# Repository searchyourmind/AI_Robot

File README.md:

# AI Robot — Raspberry Pi Vision & Motor Control

AI Robot is a four-wheel Raspberry Pi robot project combining motor control, live camera video, a browser driving interface, and AI-assisted visual observation. A shared HTTP motor service connects the browser, command-line controller, and vision process, so camera processing and user interfaces can evolve independently of motor control.

The robot platform uses a **Raspberry Pi 5, four geared DC motors, two TB6612FNG dual-channel driver boards, a Pi Camera, a USB microphone, and a speaker**. This repository contains the Python services, control logic, tests, wiring documentation, and a custom four-motor interface PCB design.

## What the project includes

- **Motor control service:** a Flask API for direction, speed, short movement commands, stopping, and control ownership.
- **Live camera and browser interface:** MJPEG video, a latest-frame snapshot endpoint, directional buttons, a speed slider, and explicit reset/arm controls.
- **Vision policy:** camera snapshots are sent to a vision model for person and stop-sign observations. An annotated video stream shows the result; the current policy can request a stop and does not initiate movement.
- **Command-line control:** a text interface for the same motor API, including speed changes and short directional commands. The `voice_ai_motor_simple.py` filename comes from earlier voice-control work; this script is currently a manual CLI.
- **Motor interface PCB:** editable KiCad schematics and layout, component selection, power calculations, wiring diagrams, BOM, and fabrication-format exports for a 12 V-class redesign.
- **Offline verification:** injected-clock and fake-GPIO tests cover the control state machine, API, clients, camera interfaces, vision parsing, and the Rev A backend lifecycle.

The motor service defaults to an in-memory **mock backend**. An opt-in **Raspberry Pi 5 / Rev A DRV8874 backend** drives the new board's GPIO, PWM, RUN, ARM, and watchdog heartbeat interface. It controls four separate bridges in left/right pairs. The backend has offline verification; the Rev A board remains a design-stage subsystem and the electrical behavior has not been bench-validated. This backend does not use the existing TB6612 harness. See the [Rev A backend guide](pi_robot/DRV8874_REVA.md).

A second opt-in backend, **`tb6612_dual`**, drives the prototype as built: two TB6612FNG boards wired directly to the Pi 5. It requires an explicit pin and polarity configuration and a duty ceiling, and ramps speed increases. It is verified offline and **has not been run on the robot**; see the [setup and first bench session](pi_robot/TB6612_DUAL.md).

## System architecture

```mermaid
flowchart LR
    CAMERA[Pi Camera] --> VIDEO[Camera service · 8090]
    VIDEO -->|MJPEG video| BROWSER[Browser controls]
    VIDEO -->|Timestamped JPEG snapshot| VISION[Vision policy · 8091]
    MODEL[Vision model] <--> VISION
    VISION --> OVERLAY[Annotated video]
    BROWSER -->|Same-origin command proxy| MOTOR[Motor API · 8088]
    CLI[Manual CLI] --> MOTOR
    VISION -->|Stop requests| MOTOR
    MOTOR --> CONTROL[Ownership / arm state / command deadlines]
    CONTROL --> BACKEND[Mock or Rev A DRV8874 backend]
    BACKEND -->|Opt-in GPIO / PWM / RUN / ARM / heartbeat| PCB[Four bridges · paired left/right commands]
```

The motor API is the command boundary. The browser and CLI request manual control; the vision process supplies observations and stop requests. A command belongs to one source/session and expires unless it is replaced by another valid command. Stopping or expiry clears the control lease. This keeps UI state, camera processing, and motor state explicit across separate processes.

## Robot hardware

| Subsystem | Project hardware |
| --- | --- |
| Compute | Raspberry Pi 5, 4 GB camera kit |
| Drivetrain | Two WHEELTEC R3 two-wheel chassis sets, giving four geared DC motors |
| Motor purchase specification | 12 V, 30:1 reduction, 500-line GMR encoder version |
| Motor drivers | Two TB6612FNG dual-channel boards |
| Batteries purchased | Two packs listed as 12 V, 2500 mAh, with built-in protection |
| Vision | Pi Camera, accessed by the camera service through OpenCV |
| Audio | USB microphone and speaker for voice-interaction experiments |

Each driver channel has its own motor connection:

| Existing driver | Channel A | Channel B |
| --- | --- | --- |
| Board A | Front-left motor | Front-right motor |
| Board B | Back-left motor | Back-right motor |

The Pi controls the existing driver boards directly; there is no Arduino in the motor-control loop. The Pi has separate power, while the motor source feeds the drivers' VM inputs. Pi ground, driver grounds, and motor-battery negative share a reference. The installed arrangement of the two purchased packs and the complete GPIO harness still need to be recorded. The purchased encoders are not yet integrated into wheel-speed feedback.

The exact motor label is still unconfirmed; MG513P30_12V is a candidate, not an established part number. Pack chemistry and actual minimum/maximum voltage also remain open. The [hardware record](hardware/rev_a/docs/actual_hardware_evidence.md) and [wiring guide](hardware/rev_a/docs/wiring_guide.md) separate the known connections from these remaining details.

## Software modules

| File | Role |
| --- | --- |
| [`web_motor.py`](pi_robot/web_motor.py) | Flask `/cmd` and `/status` endpoints; motor-service lifecycle |
| [`motor_control.py`](pi_robot/motor_control.py) | Ownership, arming, command validation, deadlines, and stop state |
| [`motor_backend.py`](pi_robot/motor_backend.py) | Backend lifecycle interface and mock motor outputs |
| [`drv8874_backend.py`](pi_robot/drv8874_backend.py) | Pi 5 GPIO, paired PWM/DIR, explicit ARM, and health-gated heartbeat for Rev A |
| [`tb6612_backend.py`](pi_robot/tb6612_backend.py) | Pi 5 GPIO for the prototype's two TB6612FNG boards: STBY, PWM/IN1/IN2, duty ceiling, and ramped starts |
| [`motor_runtime.py`](pi_robot/motor_runtime.py) | Explicit backend selection and validated hardware configuration |
| [`motor_config.py`](pi_robot/motor_config.py) | Command bounds, timeouts, and motor configuration |
| [`web_vision_drive_picam_ai.py`](pi_robot/web_vision_drive_picam_ai.py) | Camera worker, video/snapshot routes, browser UI, and motor proxy |
| [`vision_policy_daemon.py`](pi_robot/vision_policy_daemon.py) | Snapshot acquisition, model requests, observation age checks, and overlay stream |
| [`vision_safety.py`](pi_robot/vision_safety.py) | Strict observation parsing and stop-only policy |
| [`voice_ai_motor_simple.py`](pi_robot/voice_ai_motor_simple.py) | Interactive text controller using the motor API |

The camera service publishes `/stream.mjpg` for display and `/snapshot.jpg` for policy input. The policy checks frame identity and age before and after model inference. A stop sign, a near/mid-distance person, or invalid/stale input produces a stop request. A negative detection does not arm the robot or resume an earlier command. The policy's annotated output is available at `/overlay.mjpg`.

## Run the software

From the repository root, create a Python 3.10+ environment and install the application dependencies:

```sh
python3 -m venv .venv
source .venv/bin/activate
python -m pip install -r pi_robot/requirements.txt
```

Start the motor service in mock mode:

```sh
MOTOR_BACKEND=mock python pi_robot/web_motor.py
```

In another terminal using the same environment, start the CLI:

```sh
MOTOR_URL=http://127.0.0.1:8088 python pi_robot/voice_ai_motor_simple.py
```

A command sequence is:

```text
reset
arm
f
```

Send `f` within one second of `arm`; otherwise the idle lease expires. `f` requests 0.25 seconds of forward movement in the mock backend. Expiry latches stop; use `reset` and `arm` again for another movement. `s` stops and disarms; `q` stops and exits.

On a system with a configured camera, start the camera/browser service in a third terminal:

```sh
MOTOR_URL=http://127.0.0.1:8088 CAM_W=320 CAM_H=240 CAM_FPS=15 python pi_robot/web_vision_drive_picam_ai.py
```

Open `http://127.0.0.1:8090/` on that host for video and controls. The services bind to loopback by default. The [software guide](pi_robot/README.md) covers camera configuration, optional model startup, local access, environment variables, and the API. Camera startup opens a real device; motor behavior follows the separately selected backend. The [Rev A backend guide](pi_robot/DRV8874_REVA.md) covers explicit hardware configuration and first bench checks. Voice recognition, wake-word handling, and speech synthesis are not integrated into the current CLI.

## Tests

```sh
python -m pip install -r tests/hardware_mock/requirements.txt
python -m pytest tests/hardware_mock tests/hardware_gpio -q
```

The offline suites use injected clocks, fake GPIO, camera frames, HTTP/model responses, and motor outputs. Coverage includes invalid commands, ownership conflicts, expired leases, reversal sequencing, stop behavior, GPIO failures and cleanup, heartbeat/ARM sequencing, malformed vision results, stale frames, and client shutdown. These tests do not operate motors or qualify PWM timing. See the [test guide](tests/hardware_mock/README.md) and [vision integration details](docs/vision_safety_integration.md).

The combined suite passes **304 tests** (225 before the TB6612 backend was added); the [Rev A backend verification report](hardware/rev_a/validation/drv8874_backend_test_report.md) records the checks and physical validation still required.

## Custom motor-control PCB

The PCB work consolidates the prototype's jumper-wire motor, power, and control connections. A hardware-record review corrected an initial 6 V assumption to a 12 V-class design. The current board uses **four DRV8874 bridges**, one per motor, with individual current regulation, a protected common motor input, and hardware watchdog/arming logic. Front and rear motors remain commanded together by side; their power outputs are separate.

The editable design has seven schematic sheets, a provisional 100 × 100 mm two-layer layout, 121 fitted components, and 14 copper testpoints. Native checks report **ERC 0, DRC 0, unconnected 0, and schematic parity 0**. The board is a design-stage subsystem; matching it to the installed motors, packs, harness, and chassis is part of the remaining integration work.

[KiCad project and board documentation](hardware/rev_a/README.md) · [Schematic PDF](hardware/rev_a/exports/draft/schematic.pdf) · [PCB PDF](hardware/rev_a/exports/draft/pcb_layout.pdf) · [BOM](hardware/rev_a/exports/draft/bom_fitted.csv) · [3D view](hardware/rev_a/exports/draft/views/kicad_3d_render.png)

## Project documentation and next steps

- [Software setup and API](pi_robot/README.md)
- [Rev A DRV8874 hardware backend](pi_robot/DRV8874_REVA.md)
- [TB6612 prototype hardware backend and first bench session](pi_robot/TB6612_DUAL.md)
- [Project development and design decisions](docs/project_development.md)
- [Camera, vision, and client integration](docs/vision_safety_integration.md)
- [Existing and proposed wiring](hardware/rev_a/docs/wiring_guide.md)
- [Motor-driver selection](hardware/rev_a/docs/driver_margin_review.md) and [power-path design](hardware/rev_a/docs/power_path_review_12v.md)
- [PCB checks and source identities](hardware/rev_a/validation/design/design_check_report.md)

The next integration steps are to finish the actual motor/battery/harness record, bench-validate the Rev A GPIO backend and board together, integrate encoder feedback, and evaluate the custom PCB against the robot's electrical and mechanical requirements. Camera timing, vision response, motor behavior, and the audio interface remain separate areas for continued development.

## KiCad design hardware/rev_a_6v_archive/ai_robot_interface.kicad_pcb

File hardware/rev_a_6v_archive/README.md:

# AI Robot — Four-Motor PCB Design, Pre-Fabrication

**6 V REFERENCE ONLY — DIRECT 12 V INPUT INCOMPATIBLE.** The later purchase-record evidence identifies a listed 12 V motor system. D2 is a 7 V TVS, the VM overvoltage threshold is about 7.16 V, and no 12 V-to-6 V regulator exists. [Read the design-impact review](docs/12v_design_impact.md) before interpreting the preserved CAD or draft exports. A 12 V replacement design has not been completed.

**PROVISIONAL REFERENCE DESIGN — NOT VERIFIED FOR THE EXISTING ROBOT.**
**DRAFT — NOT RELEASED FOR FABRICATION.**

This project extends the existing Raspberry Pi 5 robot by consolidating its two TB6612 motor-driver boards and jumper-wire motor/power/control connections into one proposed custom board. Four motor outputs remain electrically separate. Left/right PWM and direction commands are paired between front and rear drivers; H-bridge outputs are never paralleled. Pi Camera, USB microphone and speaker remain existing Pi peripherals. Arduino is not in the confirmed motor-control loop.

The accepted reference envelope is 6.0 V nominal motor input (5.5–6.5 V), at most 0.25 A RMS per motor and 0.60 A startup peaks lasting at most 20 ms with at most 10% repetition duty, ambient at most 40 °C, separate Pi power, and a provisional 100 × 80 mm two-layer 1 oz board. These are design assumptions accepted by the user, not measured specifications of the robot. The reference additionally requires controlled supply sequencing, initial 0.10 A capacitor charging, a 3 A hard source ceiling with external overload cutoff, bounded regenerated energy, and 3.2–3.4 V logic measured at this board. See the [full operating restrictions and calculations](docs/reference_electrical_spec.md).

## Hardware matching and design explanation

The new [actual-hardware evidence audit](docs/actual_hardware_evidence.md) separates user confirmations, historical code constants and the proposed reference harness. Purchase records now describe two WHEELTEC R3 sets with four 12 V / 30:1 / 500-line GMR motors, two regulated TB6612 boards, two listed 12 V / 2500 mAh protected packs, and a Pi 5 4 GB camera kit. Exact motor identity/current profiles, actual pack voltage bounds/topology, two-module GPIO/VCC wiring and protection behavior remain unknown. MG513P30_12V is a candidate only. Compatibility is now a known voltage mismatch for direct 12 V input, not merely an unknown.

The [wiring guide](docs/wiring_guide.md) contains separate existing/proposed diagrams, four motor-connector mappings and the proposed Pi-to-J6 table. [Design decisions](docs/design_decisions.md) explains all eleven major choices and their tradeoffs. The [component-count review](docs/component_count_review.md) accounts for all 97 placements and identifies simplification candidates: 62 parts serve signal conditioning and permission/supervision beyond basic wiring consolidation.

The delivered board physically shares left/right command inputs; it does not provide four independent wheel commands. SW1 inhibits STBY and clears the arm latch while the logic operates; it does not interrupt VM power. The new RUN/ARM/heartbeat protocol remains unimplemented in a real GPIO backend.

## Editable design and review records

| Item | Evidence |
|---|---|
| Native KiCad 10 project | [Project](ai_robot_interface.kicad_pro), [five-sheet schematic](ai_robot_interface.kicad_sch), [PCB](ai_robot_interface.kicad_pcb) |
| Confirmed facts versus assumptions | [Requirements table](docs/requirements_assumptions.md), [scope](docs/scope_design_only.md) |
| Circuit | [Power circuit](docs/power_circuit_spec.md), [hardware enable and watchdog](docs/enable_interface_spec.md) |
| Pins and packages | [Wheel/header mapping](docs/pin_map.md), [footprint review](docs/footprint_review.md), [project-local libraries](libraries/README.md) |
| Calculations and layout | [Electrical reference budget](docs/reference_electrical_spec.md), [routing rationale](docs/routing_rationale.md) |
| Candidate BOM | [Grouped BOM](exports/draft/bom_reference.tsv), [per-reference BOM](exports/draft/bom_per_reference.tsv), [BOM review](docs/bom_review.md) |
| Manufacturing preparation | [Draft package](exports/draft/README.md), [fabrication notes](docs/fabrication_notes.md), [assembly notes](docs/assembly_notes.md) |
| Deferred physical work | [Bring-up procedure](validation/bring_up.md), [blank test records](validation/physical_test_records.csv) |
| Status and reproducibility | [Progress](PROGRESS.md), [KiCad workflow](docs/cad_workflow.md) |

```mermaid
flowchart LR
  P[Separate Pi supply] --> PI[Raspberry Pi 5]
  PI -->|3.3 V logic / common ground| L[Buffers / rail monitor / arm latch / watchdog]
  PI -->|Paired left-right commands| L
  S[Physical enable switch] --> L
  B[Bounded 6 V motor source] --> X[Fuse / reverse blocker / gated feed / bulk and TVS]
  X --> U1[U1 front TB6612]
  X --> U2[U2 rear TB6612]
  L -->|Six command lines plus gated STBY| U1
  L -->|Same commands / separate outputs| U2
  U1 --> FL[Front left]
  U1 --> FR[Front right]
  U2 --> BL[Back left]
  U2 --> BR[Back right]
```

Hardware permission requires valid logic and motor rails, the physical switch, a live watchdog, RUN_REQ and a new arm edge. A fault clears the latch. The 170–230 ms watchdog is a separate circuit; the Python command-expiry tests do not validate it. J6 is a custom logic cable, **not a Raspberry Pi 40-pin HAT connector**. The new ARM/RUN/heartbeat hardware protocol has not been integrated into a physical GPIO backend.

## Actual design checks and views

KiCad 10.0.6: **0 ERC violations, 0 DRC violations, 0 unconnected items, 0 schematic parity issues**. No DRC rule class is ignored. ERC's SPICE-model check is outside scope. The [check report](validation/design/design_check_report.md), [native command log](validation/design/command_log.json) and [independent pad/net review](validation/design/electrical_board_review.json) preserve the evidence and limitations.

*KiCad-generated render with nominal/generic package models. No physical board was built.*

The native schematic has five sheets and 107 electrical items, including 10 copper test points. The candidate assembly BOM and placement file contain 97 components / 33 distinct MPNs. Four board-only mounting holes are excluded from assembly. [Schematic PDF](exports/draft/schematic.pdf), [copper-layer PDF](exports/draft/pcb_layout.pdf), and [assembly drawing](exports/draft/assembly_top.pdf) are draft review documents.

## Evidence boundaries

- Existing robot/prototype descriptions are historical evidence and user reports; they do not demonstrate the proposed PCB.
- The previous [132 offline mock tests](validation/software_test_report.md) and original JUnit report are retained unchanged. No new software test count is presented as hardware validation.
- Native CAD checks and exports are recorded separately under `validation/design/`. ERC/DRC do not prove electrical safety, thermal behavior, software integration or operation.
- Fabrication: **DEFERRED / NOT BUILT**. Assembly: **DEFERRED / NOT ASSEMBLED**. Physical validation: **NOT TESTED**. Integration with the proposed PCB: **NOT TESTED**.
- The listed motor voltage/ratio and encoder presence are purchase-confirmed. Exact motor identity and current, pack voltage bounds/protection behavior/topology, real GPIO harness/polarity, enclosure and mounting constraints remain unknown. Abrupt Pi power loss while VM is charged is not covered by the reference sequence. No automatic battery hot-plug, current limiting per motor, encoder support, certified emergency-stop function or HAT compliance is claimed.

The motor software remains mock-only and AI has stop-only authority; consult the [software/API guide](docs/software_safety_api.md) and [vision/client guide](../../docs/vision_safety_integration.md). Design artifacts were produced with AI assistance and require the student's engineering review and independent physical validation. No vendor has been contacted and nothing has been ordered, pushed, deployed or released.

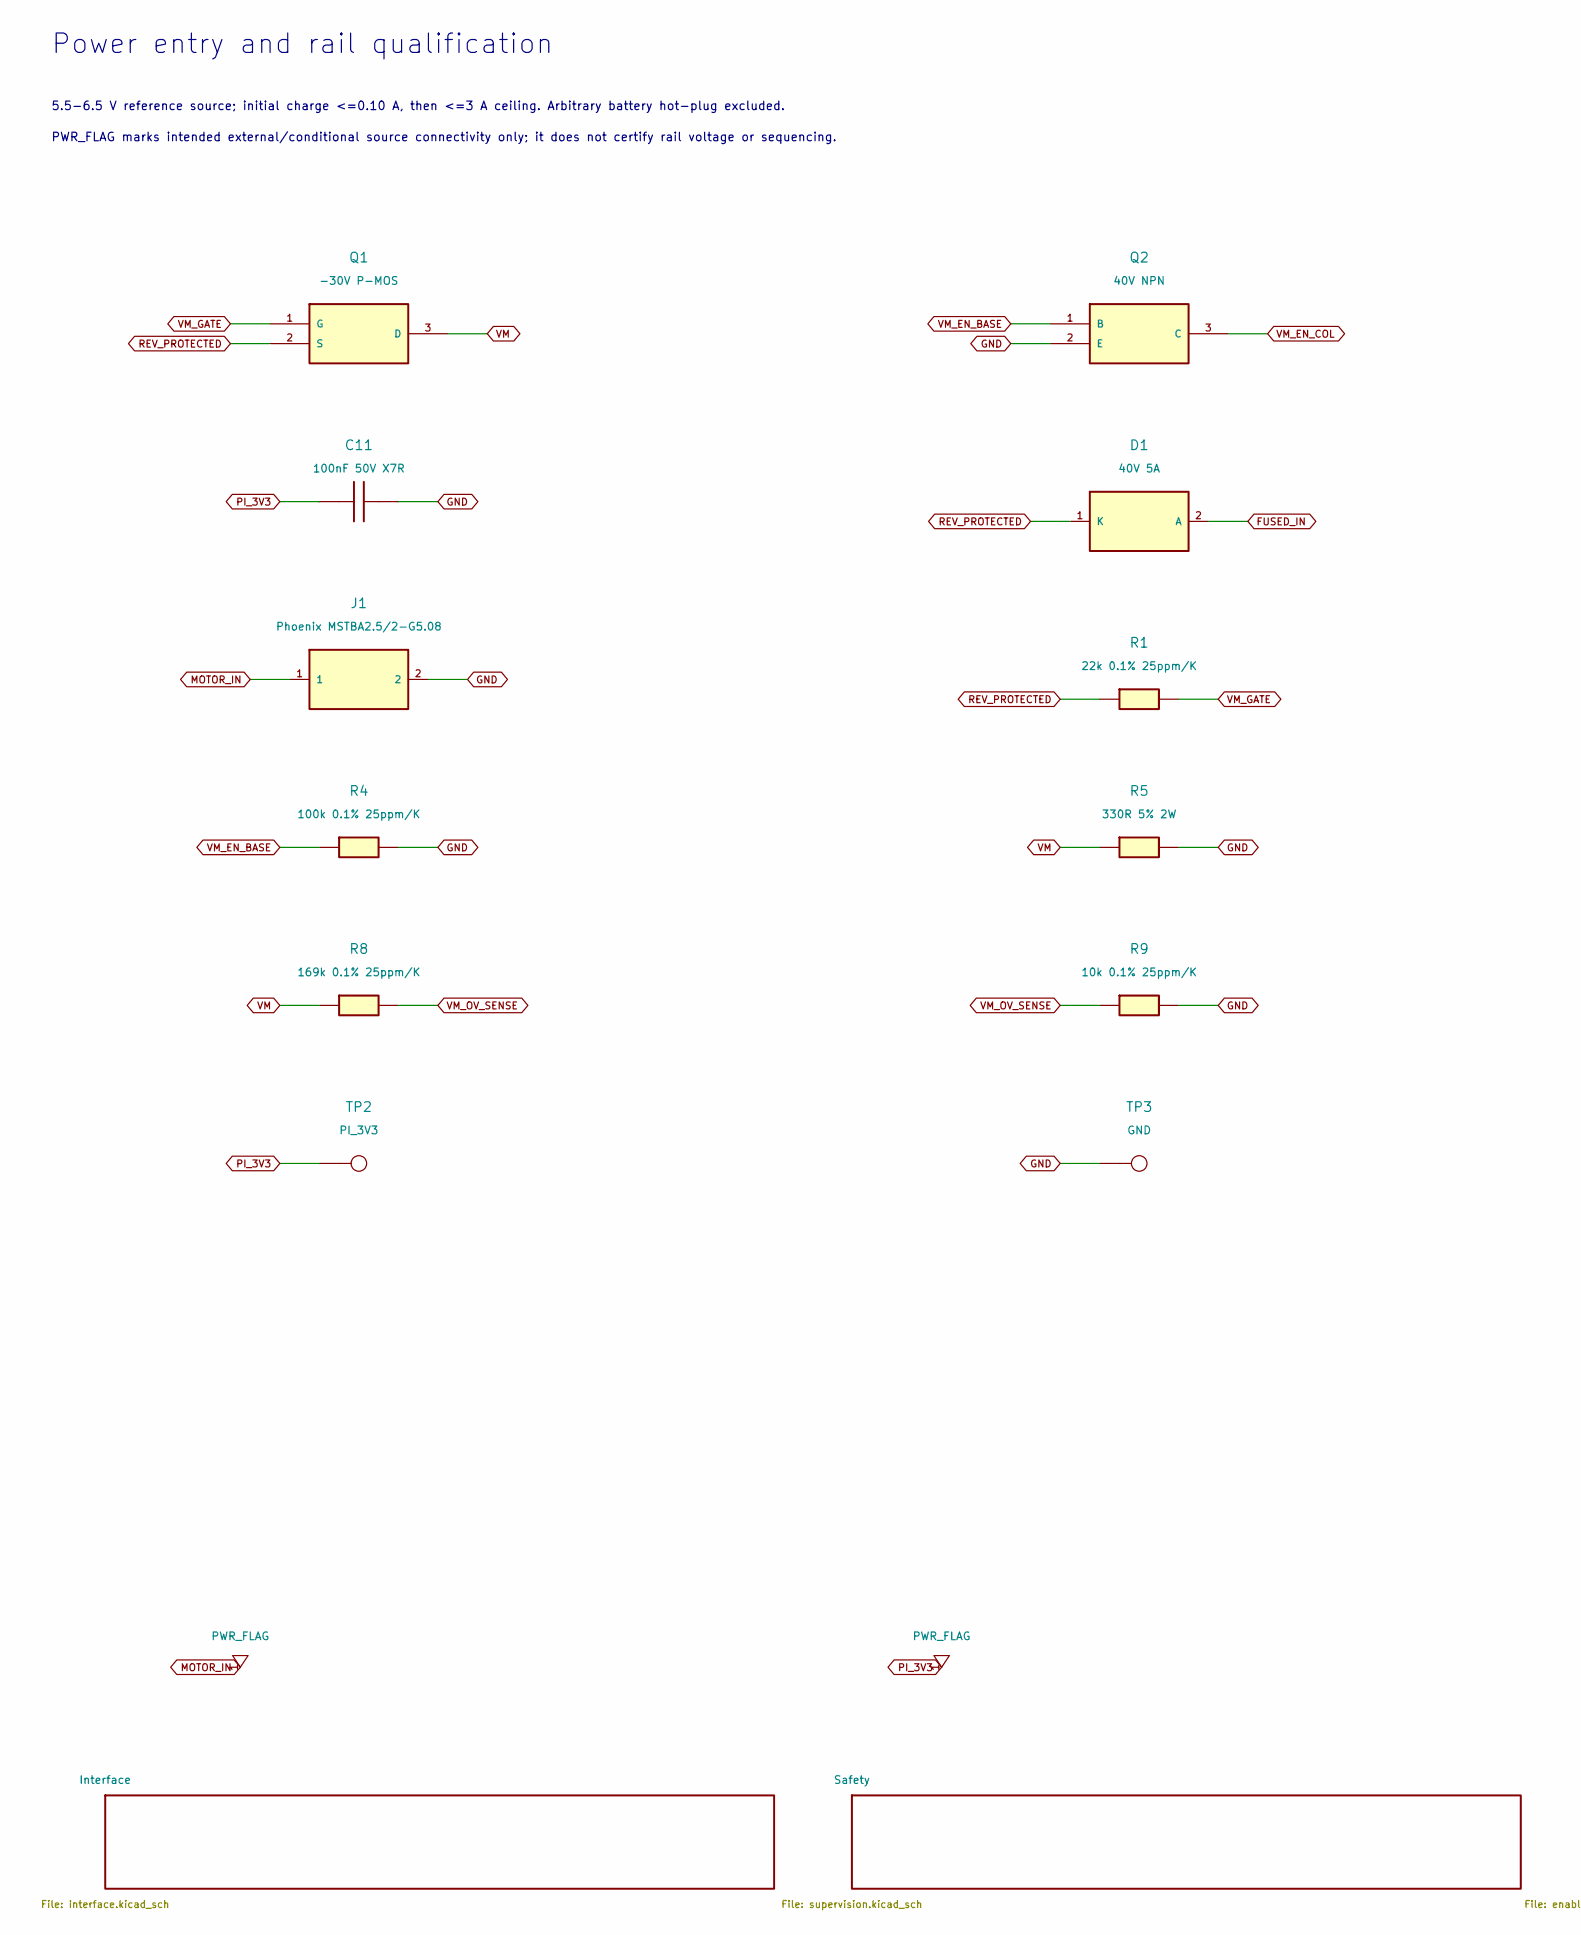
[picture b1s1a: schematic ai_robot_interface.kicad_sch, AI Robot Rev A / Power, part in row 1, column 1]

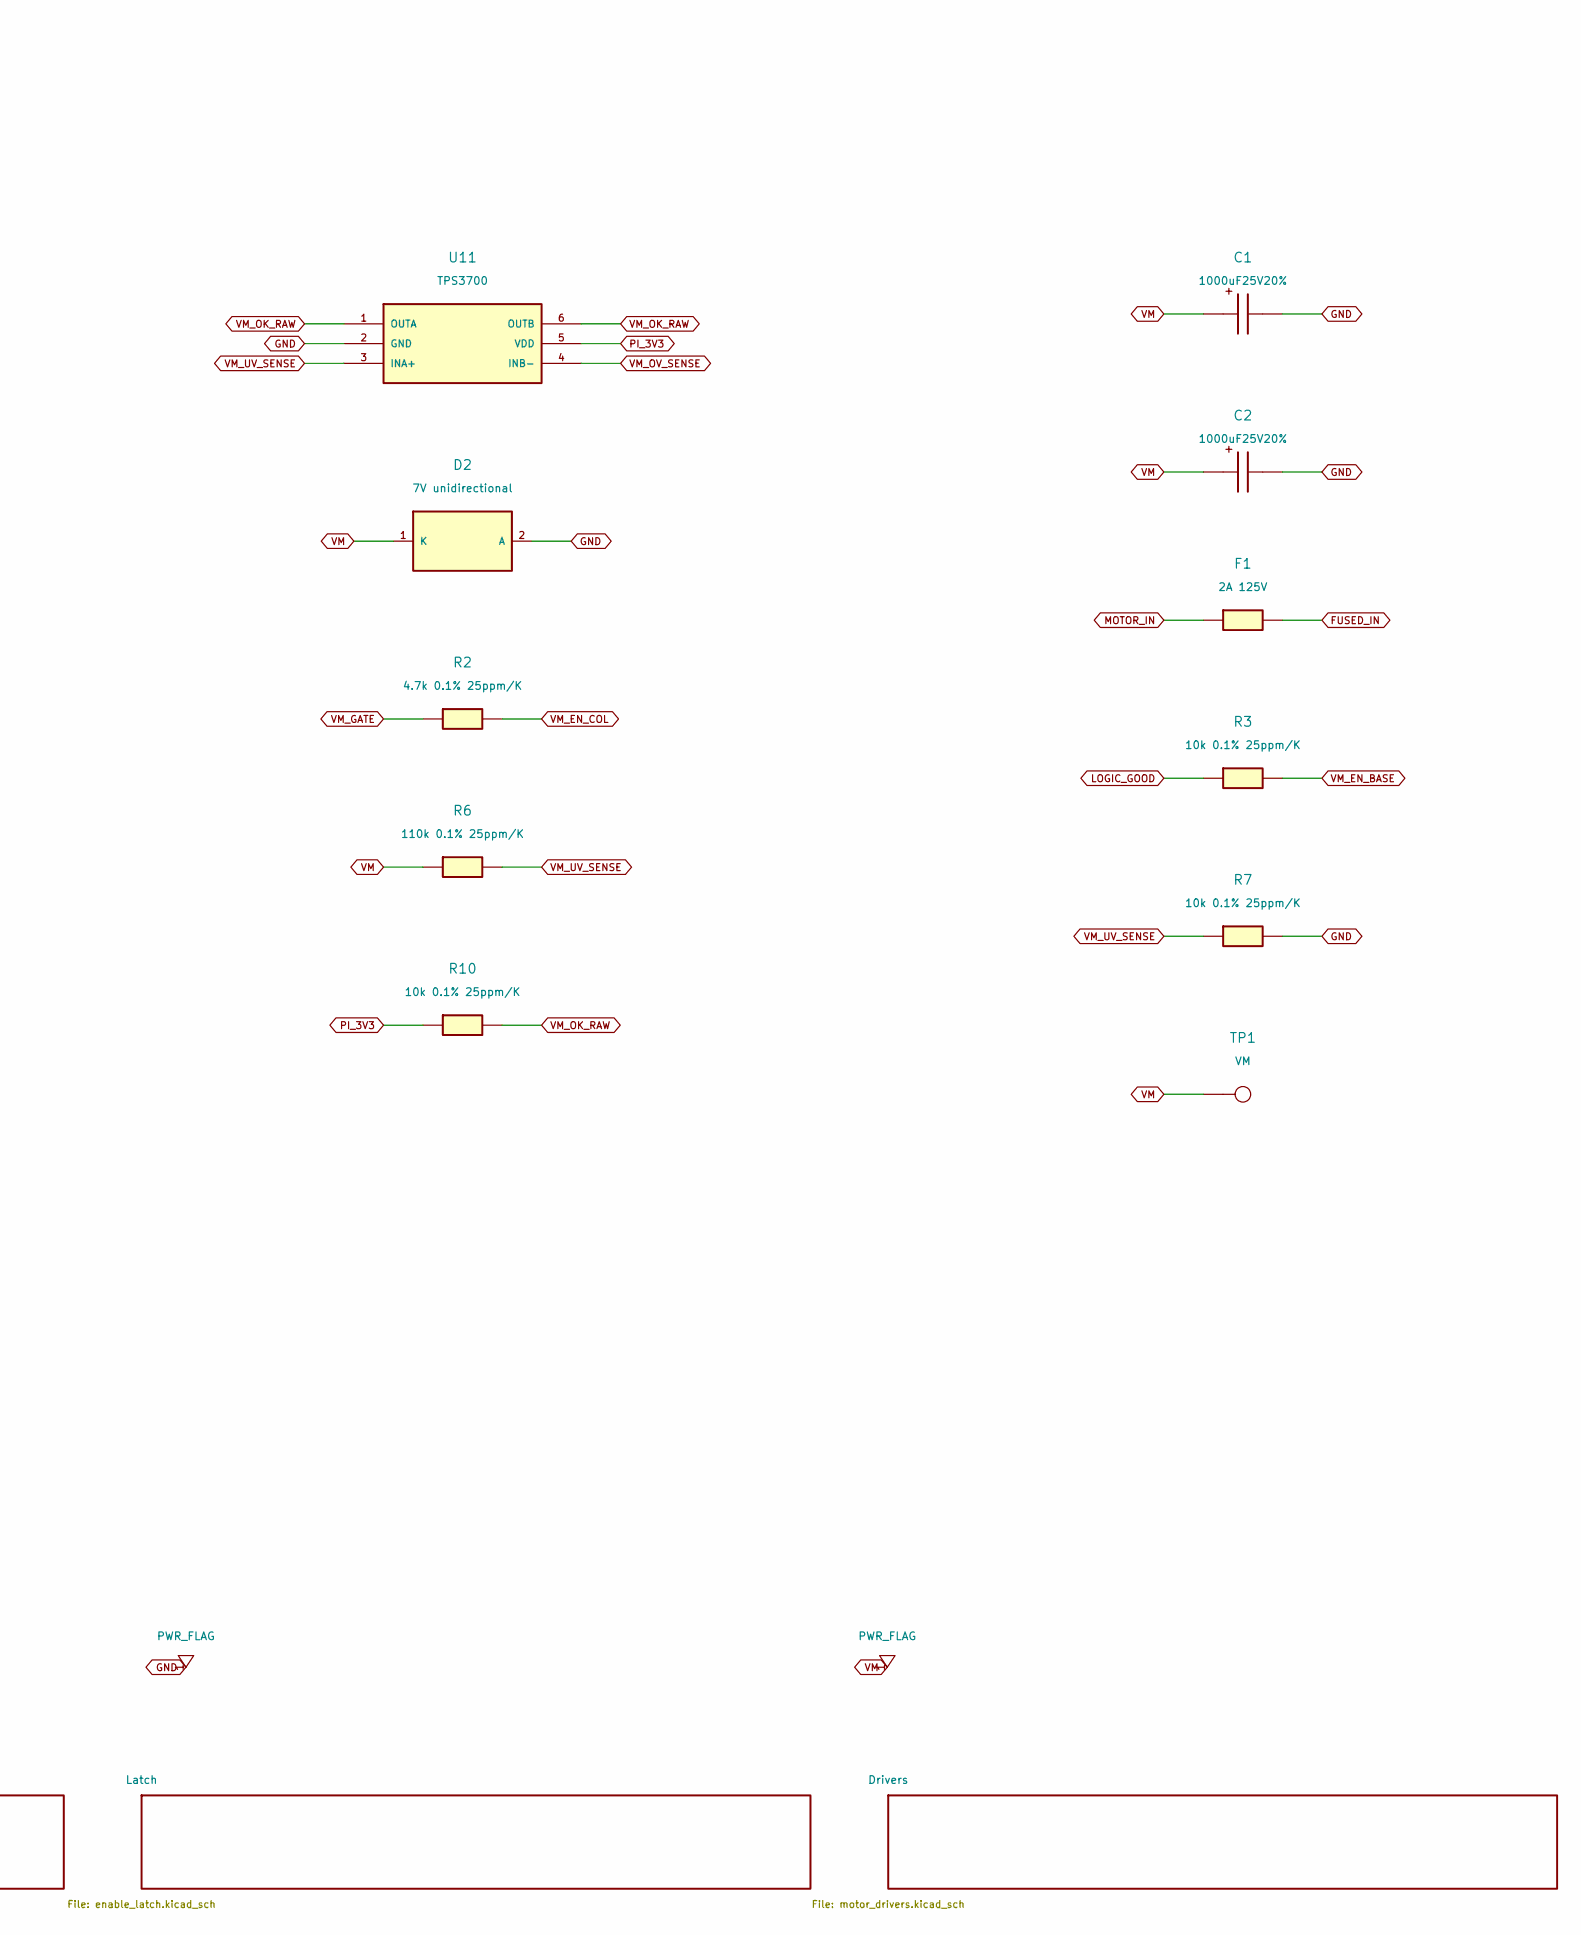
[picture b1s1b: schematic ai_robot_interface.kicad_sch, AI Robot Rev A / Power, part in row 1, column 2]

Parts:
C1, C2: 1000uF25V20%; CP_Radial_D10.0mm_P5.00mm; MPN EEUFR1E102
C11: 100nF 50V X7R; C_0805_2012Metric; MPN C0805C104K5RACTU
D1: 40V 5A; D_SMC; MPN SSC54-E3/57T
D2: 7V unidirectional; D_SMB; MPN SMBJ7.0A
F1: 2A 125V; Fuse_Littelfuse_451; MPN 0451002.MRL
J1: Phoenix MSTBA2.5/2-G5.08; PhoenixContact_MSTBA_2,5_2-G-5,08_1x02_P5.08mm_Horizontal; MPN 1757242
Q1: -30V P-MOS; SOT-23; MPN AO3401A
Q2: 40V NPN; SOT-23; MPN MMBT3904LT1G
R1: 22k 0.1% 25ppm/K; R_0805_2012Metric; MPN TNPW080522K0BEEA
R2: 4.7k 0.1% 25ppm/K; R_0805_2012Metric; MPN TNPW08054K70BEEA
R3, R7, R9, R10: 10k 0.1% 25ppm/K; R_0805_2012Metric; MPN TNPW080510K0BEEA
R4: 100k 0.1% 25ppm/K; R_0805_2012Metric; MPN TNPW0805100KBEEA
R5: 330R 5% 2W; R_Axial_DIN0414_L11.9mm_D4.5mm_P15.24mm_Horizontal; MPN PR02000203300JA100
R6: 110k 0.1% 25ppm/K; R_0805_2012Metric; MPN TNPW0805110KBEEA
R8: 169k 0.1% 25ppm/K; R_0805_2012Metric; MPN TNPW0805169KBEEA
TP1: VM; TestPoint_Pad_D1.5mm; MPN PCB_COPPER_FEATURE
TP2: PI_3V3; TestPoint_Pad_D1.5mm; MPN PCB_COPPER_FEATURE
TP3: GND; TestPoint_Pad_D1.5mm; MPN PCB_COPPER_FEATURE
U11: TPS3700; SOT-23-6; MPN TPS3700DDCR

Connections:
FUSED_IN: D1.2 (A), F1.2
GND: C1.2, C2.2, C11.2, D2.2 (A), J1.2, Q2.2 (E), R4.2, R5.2, R7.2, R9.2, TP3.1, U11.2 (GND); also elsewhere on the board
LOGIC_GOOD: R3.1; also elsewhere on the board
MOTOR_IN: F1.1, J1.1
PI_3V3: C11.1, R10.1, TP2.1, U11.5 (VDD); also elsewhere on the board
REV_PROTECTED: D1.1 (K), Q1.2 (S), R1.1
VM: C1.1, C2.1, D2.1 (K), Q1.3 (D), R5.1, R6.1, R8.1, TP1.1; also elsewhere on the board
VM_EN_BASE: Q2.1 (B), R3.2, R4.1
VM_EN_COL: Q2.3 (C), R2.2
VM_GATE: Q1.1 (G), R1.2, R2.1
VM_OK_RAW: R10.2, U11.1 (OUTA), U11.6 (OUTB); also elsewhere on the board
VM_OV_SENSE: R8.2, R9.1, U11.4 (INB-)
VM_UV_SENSE: R6.2, R7.1, U11.3 (INA+)

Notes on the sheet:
Power entry and rail qualification
5.5-6.5 V reference source; initial charge <=0.10 A, then <=3 A ceiling. Arbitrary battery hot-plug excluded.
PWR_FLAG marks intended external/conditional source connectivity only; it does not certify rail voltage or sequencing.

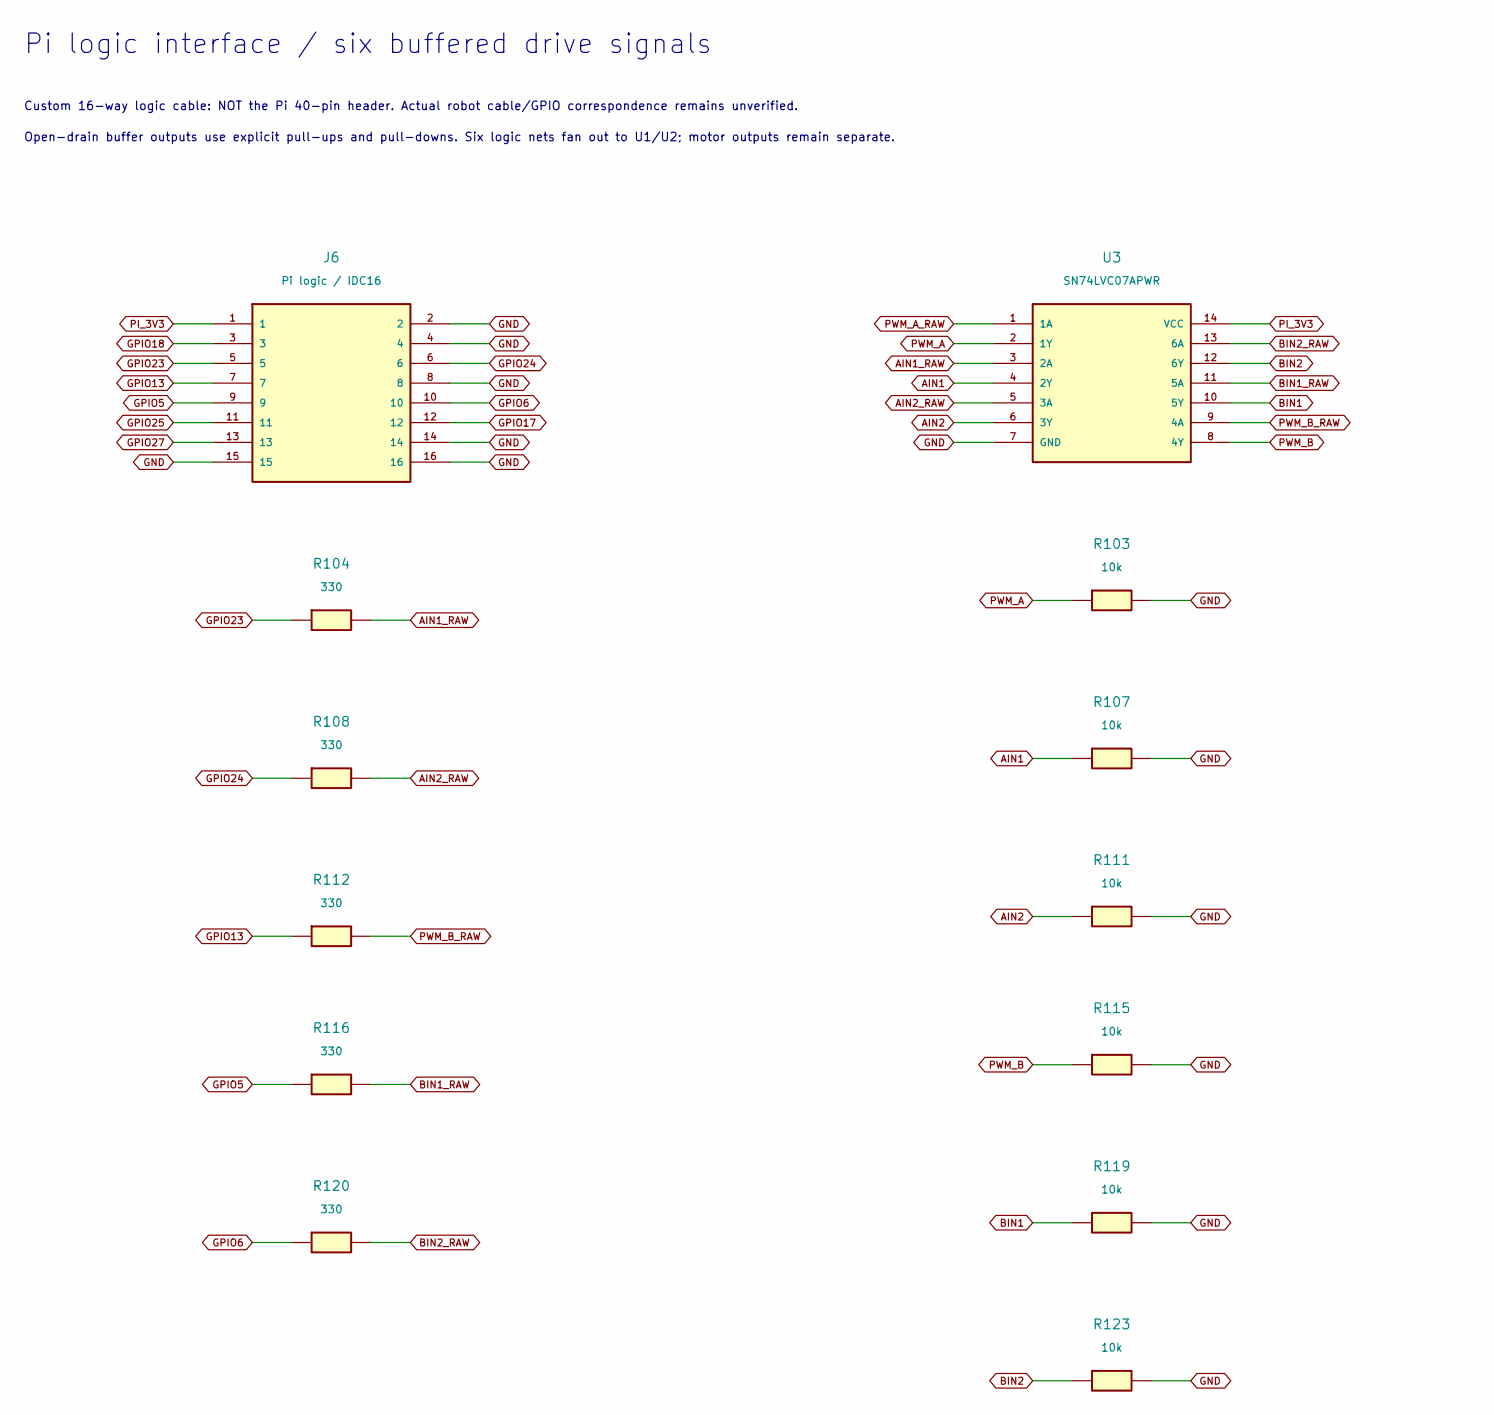
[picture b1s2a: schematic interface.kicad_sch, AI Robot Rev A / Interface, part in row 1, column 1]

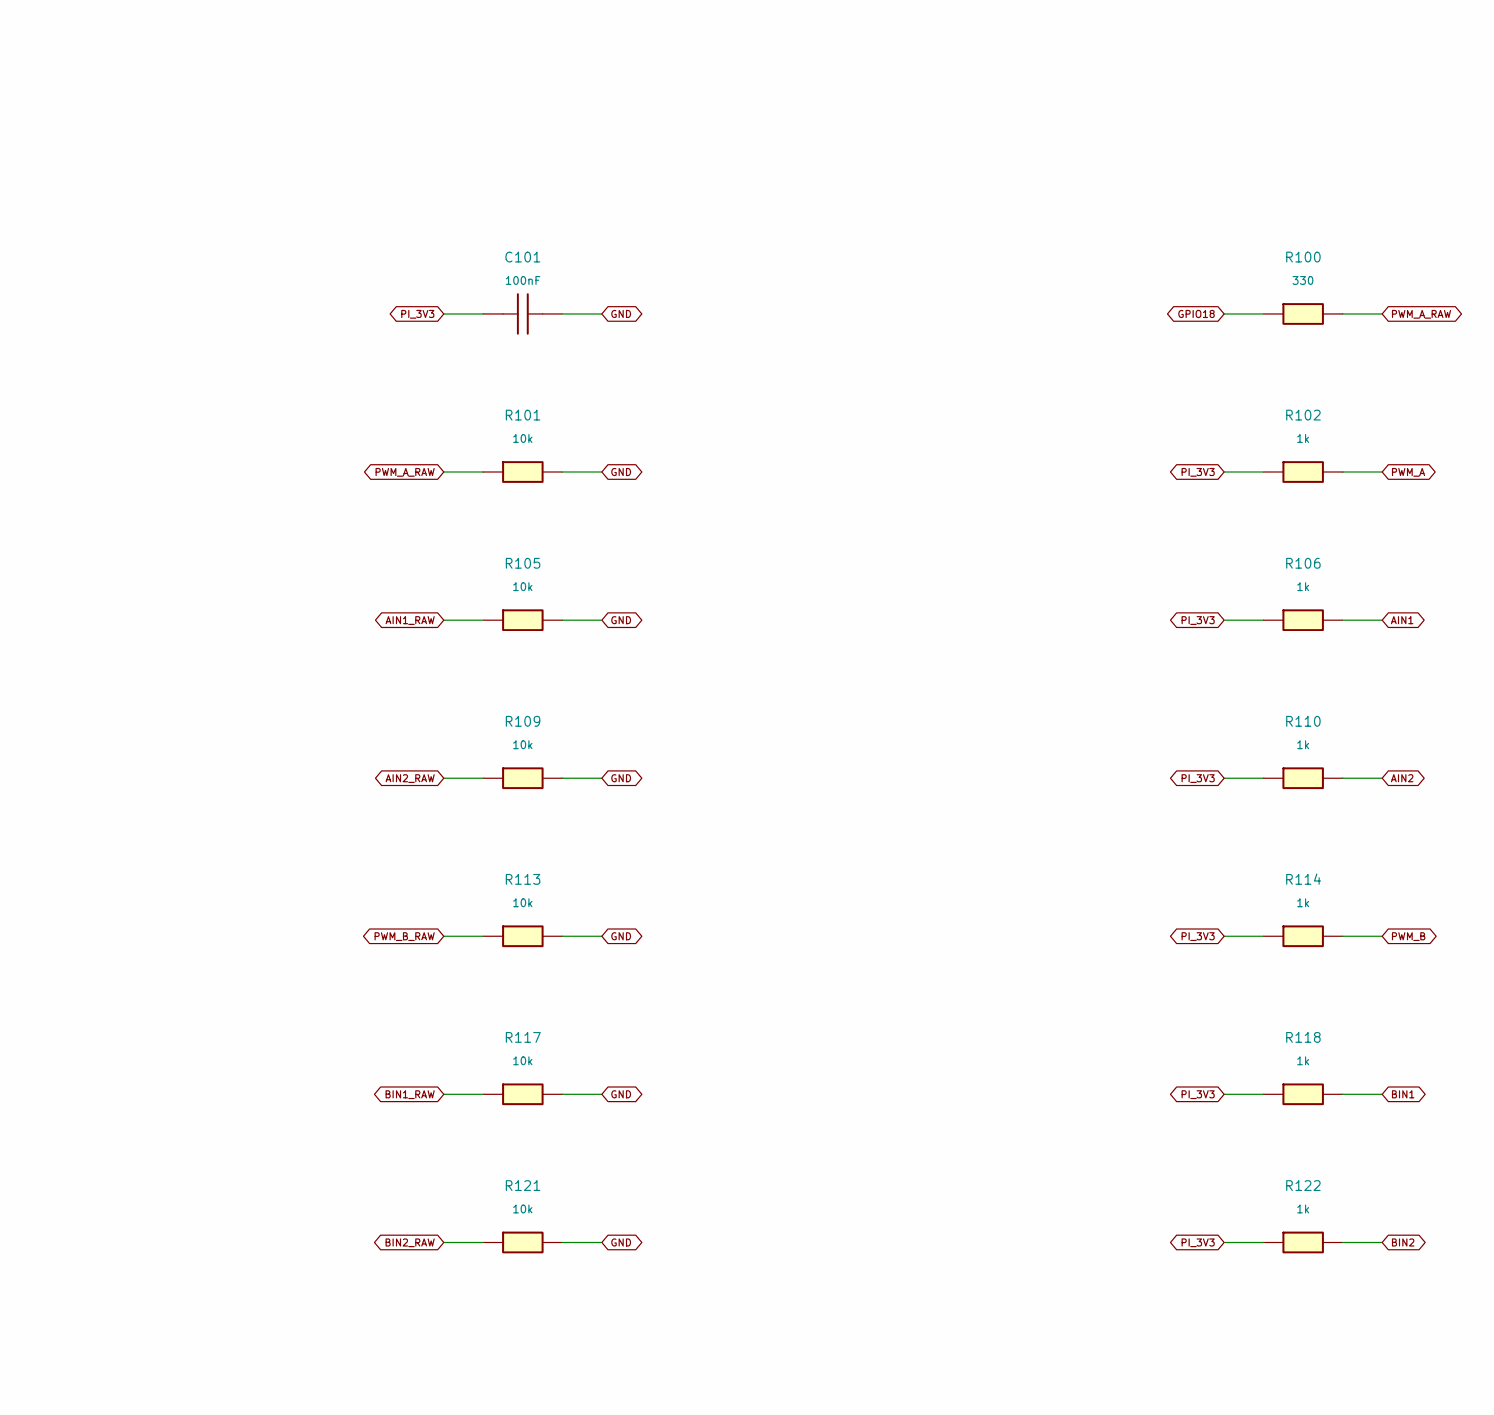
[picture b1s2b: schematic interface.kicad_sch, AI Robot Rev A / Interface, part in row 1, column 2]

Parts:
C101: 100nF; C_0603_1608Metric; MPN CC0603KRX7R9BB104
J6: Pi logic / IDC16; IDC_Wurth_61201621621; MPN 61201621621
R100, R104, R108, R112, R116, R120: 330; R_0603_1608Metric; MPN RC0603FR-07330RL
R101, R103, R105, R107, R109, R111, R113, R115, R117, R119, R121, R123: 10k; R_0603_1608Metric; MPN RC0603FR-0710KL
R102, R106, R110, R114, R118, R122: 1k; R_0603_1608Metric; MPN RC0603FR-071KL
U3: SN74LVC07APWR; TSSOP-14_4.4x5mm_P0.65mm; MPN SN74LVC07APWR

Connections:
AIN1: R106.2, R107.1, U3.4 (2Y); also elsewhere on the board
AIN1_RAW: R104.2, R105.1, U3.3 (2A)
AIN2: R110.2, R111.1, U3.6 (3Y); also elsewhere on the board
AIN2_RAW: R108.2, R109.1, U3.5 (3A)
BIN1: R118.2, R119.1, U3.10 (5Y); also elsewhere on the board
BIN1_RAW: R116.2, R117.1, U3.11 (5A)
BIN2: R122.2, R123.1, U3.12 (6Y); also elsewhere on the board
BIN2_RAW: R120.2, R121.1, U3.13 (6A)
GND: C101.2, J6.2, J6.4, J6.8, J6.14, J6.15, J6.16, R101.2, R103.2, R105.2, R107.2, R109.2, R111.2, R113.2, R115.2, R117.2, R119.2, R121.2, R123.2, U3.7 (GND); also elsewhere on the board
GPIO5: J6.9, R116.1
GPIO6: J6.10, R120.1
GPIO13: J6.7, R112.1
GPIO17: J6.12; also elsewhere on the board
GPIO18: J6.3, R100.1
GPIO23: J6.5, R104.1
GPIO24: J6.6, R108.1
GPIO25: J6.11; also elsewhere on the board
GPIO27: J6.13; also elsewhere on the board
PI_3V3: C101.1, J6.1, R102.1, R106.1, R110.1, R114.1, R118.1, R122.1, U3.14 (VCC); also elsewhere on the board
PWM_A: R102.2, R103.1, U3.2 (1Y); also elsewhere on the board
PWM_A_RAW: R100.2, R101.1, U3.1 (1A)
PWM_B: R114.2, R115.1, U3.8 (4Y); also elsewhere on the board
PWM_B_RAW: R112.2, R113.1, U3.9 (4A)

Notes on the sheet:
Pi logic interface / six buffered drive signals
Custom 16-way logic cable: NOT the Pi 40-pin header. Actual robot cable/GPIO correspondence remains unverified.
Open-drain buffer outputs use explicit pull-ups and pull-downs. Six logic nets fan out to U1/U2; motor outputs remain separate.
